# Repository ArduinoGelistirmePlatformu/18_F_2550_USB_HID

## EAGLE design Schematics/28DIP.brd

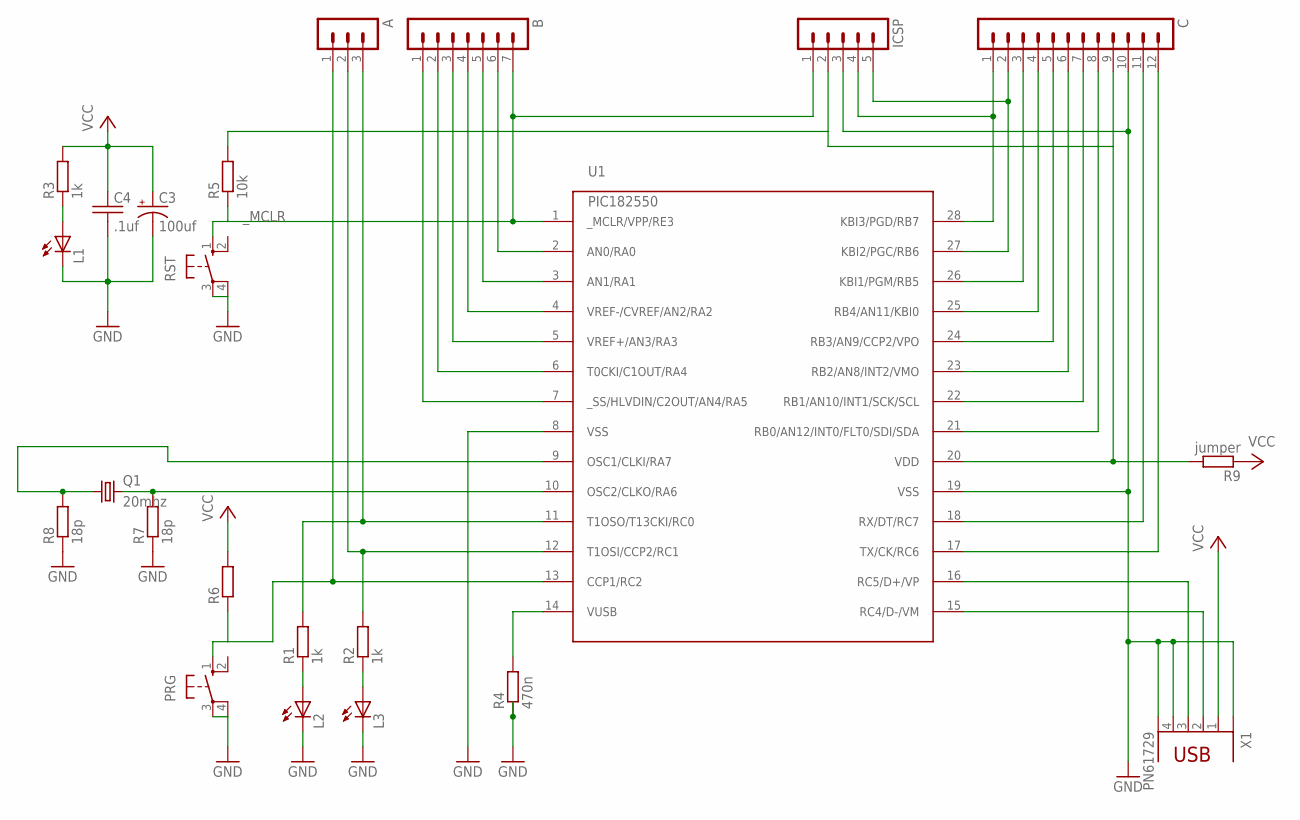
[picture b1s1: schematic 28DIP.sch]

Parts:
A: MA03-1
B: MA07-1
C: MA12-1
C3: 100uf; CAP_0200ELECTROLYTIC_0250
C4: .1uf; CAP_0100
ICSP: MA05-1
L1, L2, L3: LED; LED5MM
PRG: 10-XX; B3F-10XX
Q1: 20mhz; HC49/S
R1, R2, R3: 1k; M0805
R4: 470n; M0805
R5: 10k; M0805
R6: R-EU_M0805; M0805
R7, R8: 18p; M0805
R9: jumper; M1206
RST: 10-XX; B3F-10XX
U1: PIC182550; DIL28-3
X1: PN61729

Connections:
GND: C.10, C3.-, C4.2, ICSP.3, L1.K (C), L2.K (C), L3.K (C), PRG.3, PRG.4 (P1), R4.1, R7.1, R8.1, RST.3, RST.4 (P1), U1.8 (VSS), U1.19 (VSS), X1.4, X1.GND1 (G1), X1.GND2 (G2)
unnamed: U1.16 (RC5/D+/VP), X1.3
unnamed: C.9, ICSP.2, R5.2, R9.2, U1.20 (VDD)
unnamed: U1.15 (RC4/D-/VM), X1.2
unnamed: R4.2, U1.14 (VUSB)
unnamed: L2.A, R1.1
unnamed: A.1, PRG.1 (S), R6.1, U1.13 (CCP1/RC2)
unnamed: L3.A, R2.1
unnamed: L1.A, R3.1
unnamed: A.3, R1.2, U1.11 (T1OSO/T13CKI/RC0)
unnamed: A.2, R2.2, U1.12 (T1OSI/CCP2/RC1)
unnamed: C.1, ICSP.4, U1.28 (KBI3/PGD/RB7)
unnamed: C.2, ICSP.5, U1.27 (KBI2/PGC/RB6)
unnamed: C.3, U1.26 (KBI1/PGM/RB5)
unnamed: C.4, U1.25 (RB4/AN11/KBI0)
unnamed: C.5, U1.24 (RB3/AN9/CCP2/VPO)
unnamed: C.6, U1.23 (RB2/AN8/INT2/VMO)
unnamed: C.7, U1.22 (RB1/AN10/INT1/SCK/SCL)
unnamed: C.8, U1.21 (RB0/AN12/INT0/FLT0/SDI/SDA)
unnamed: B.6, U1.2 (AN0/RA0)
unnamed: B.5, U1.3 (AN1/RA1)
unnamed: B.4, U1.4 (VREF-/CVREF/AN2/RA2)
unnamed: B.3, U1.5 (VREF+/AN3/RA3)
unnamed: B.2, U1.6 (T0CKI/C1OUT/RA4)
unnamed: B.1, U1.7 (_SS/HLVDIN/C2OUT/AN4/RA5)
unnamed: C.12, U1.17 (TX/CK/RC6)
unnamed: C.11, U1.18 (RX/DT/RC7)
unnamed: Q1.2, R7.2, U1.10 (OSC2/CLKO/RA6)
unnamed: Q1.1, R8.2, U1.9 (OSC1/CLKI/RA7)
VCC: C3.+, C4.1, R3.2, R6.2, R9.1, X1.1
_MCLR: B.7, ICSP.1, R5.1, RST.1 (S), U1.1 (_MCLR/VPP/RE3)

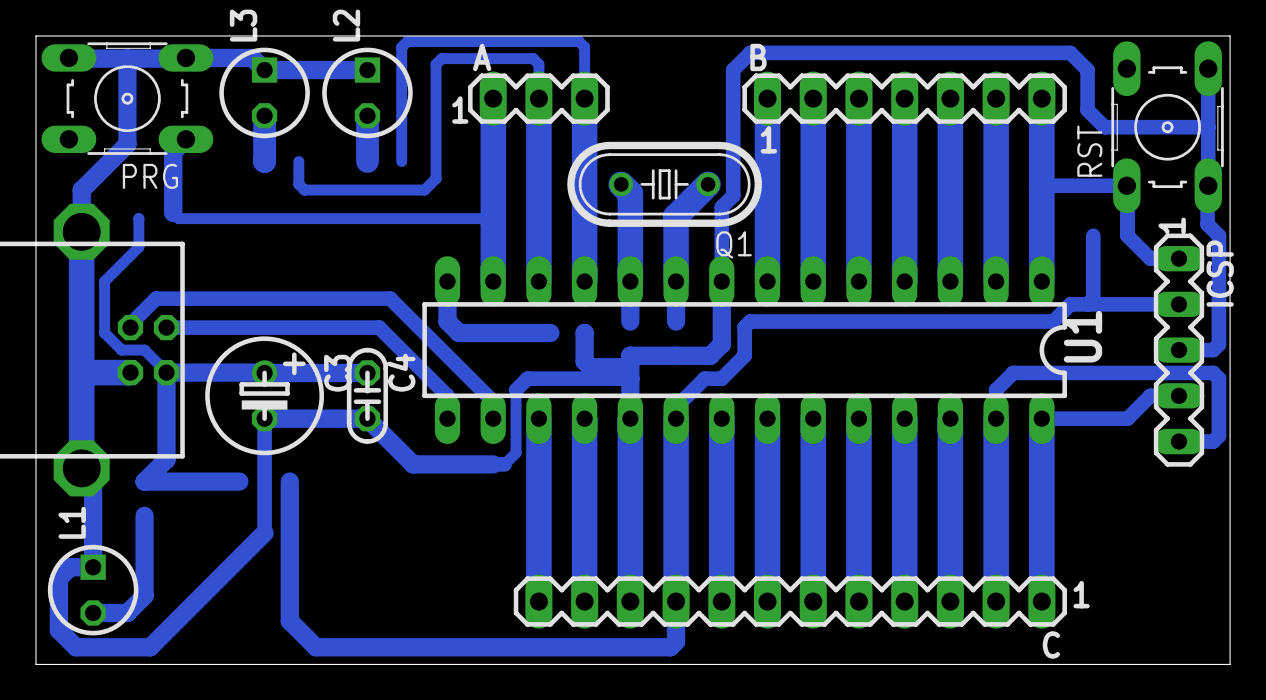
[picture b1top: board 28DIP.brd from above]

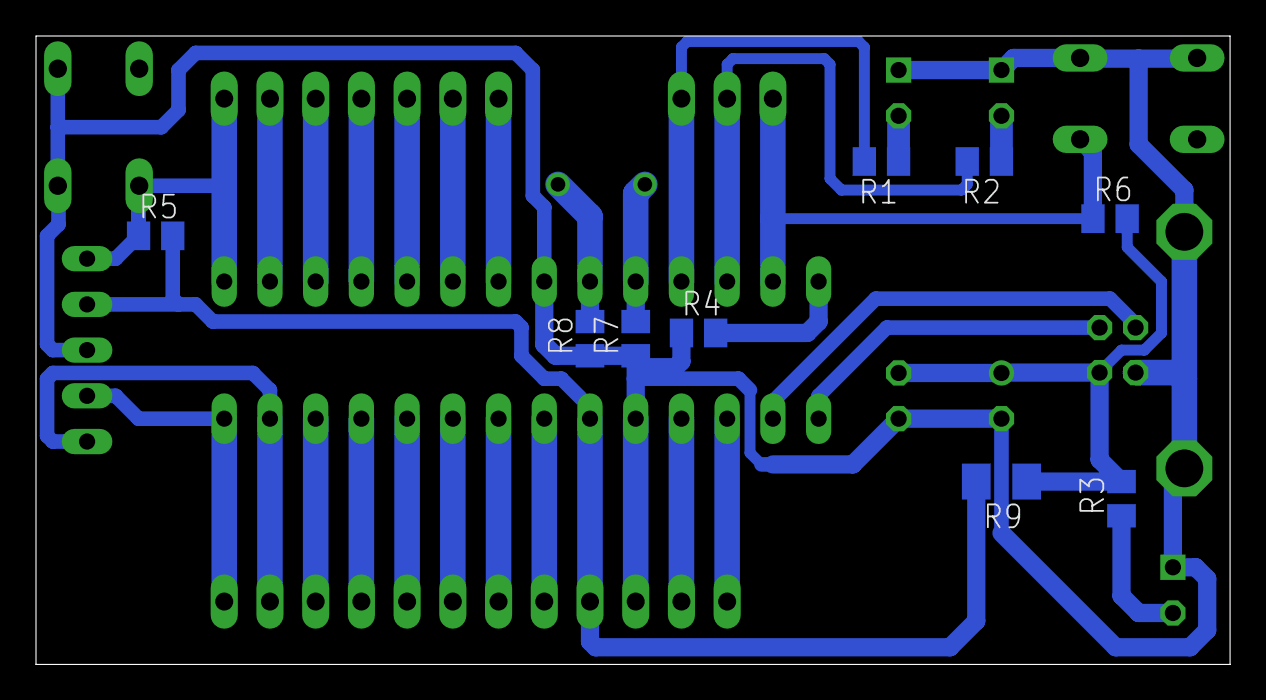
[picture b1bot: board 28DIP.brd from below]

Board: 2 copper layers, 66.3 x 34.9 mm, 23 parts (9 on the bottom side), 31 nets.

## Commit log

2017-05-08 :boom::camel: Added .gitattributes & .gitignore files
2017-05-08 18F2550 USB Bootloader HID
    18F2550 USB Bootloader HID
2017-05-08 18F2550 USB HID
    18F2550 USB Bootloader HID
